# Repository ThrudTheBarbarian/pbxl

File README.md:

# pbxl
Experiment in using an XMOS chip for a low latency serial connection to enable a parallel bus expansion on the Atari XL/XE

# Website
This is very much a work-in-progress, but the website rendered from the source herein [is available here](http://pbxl.oobergeek.net/)

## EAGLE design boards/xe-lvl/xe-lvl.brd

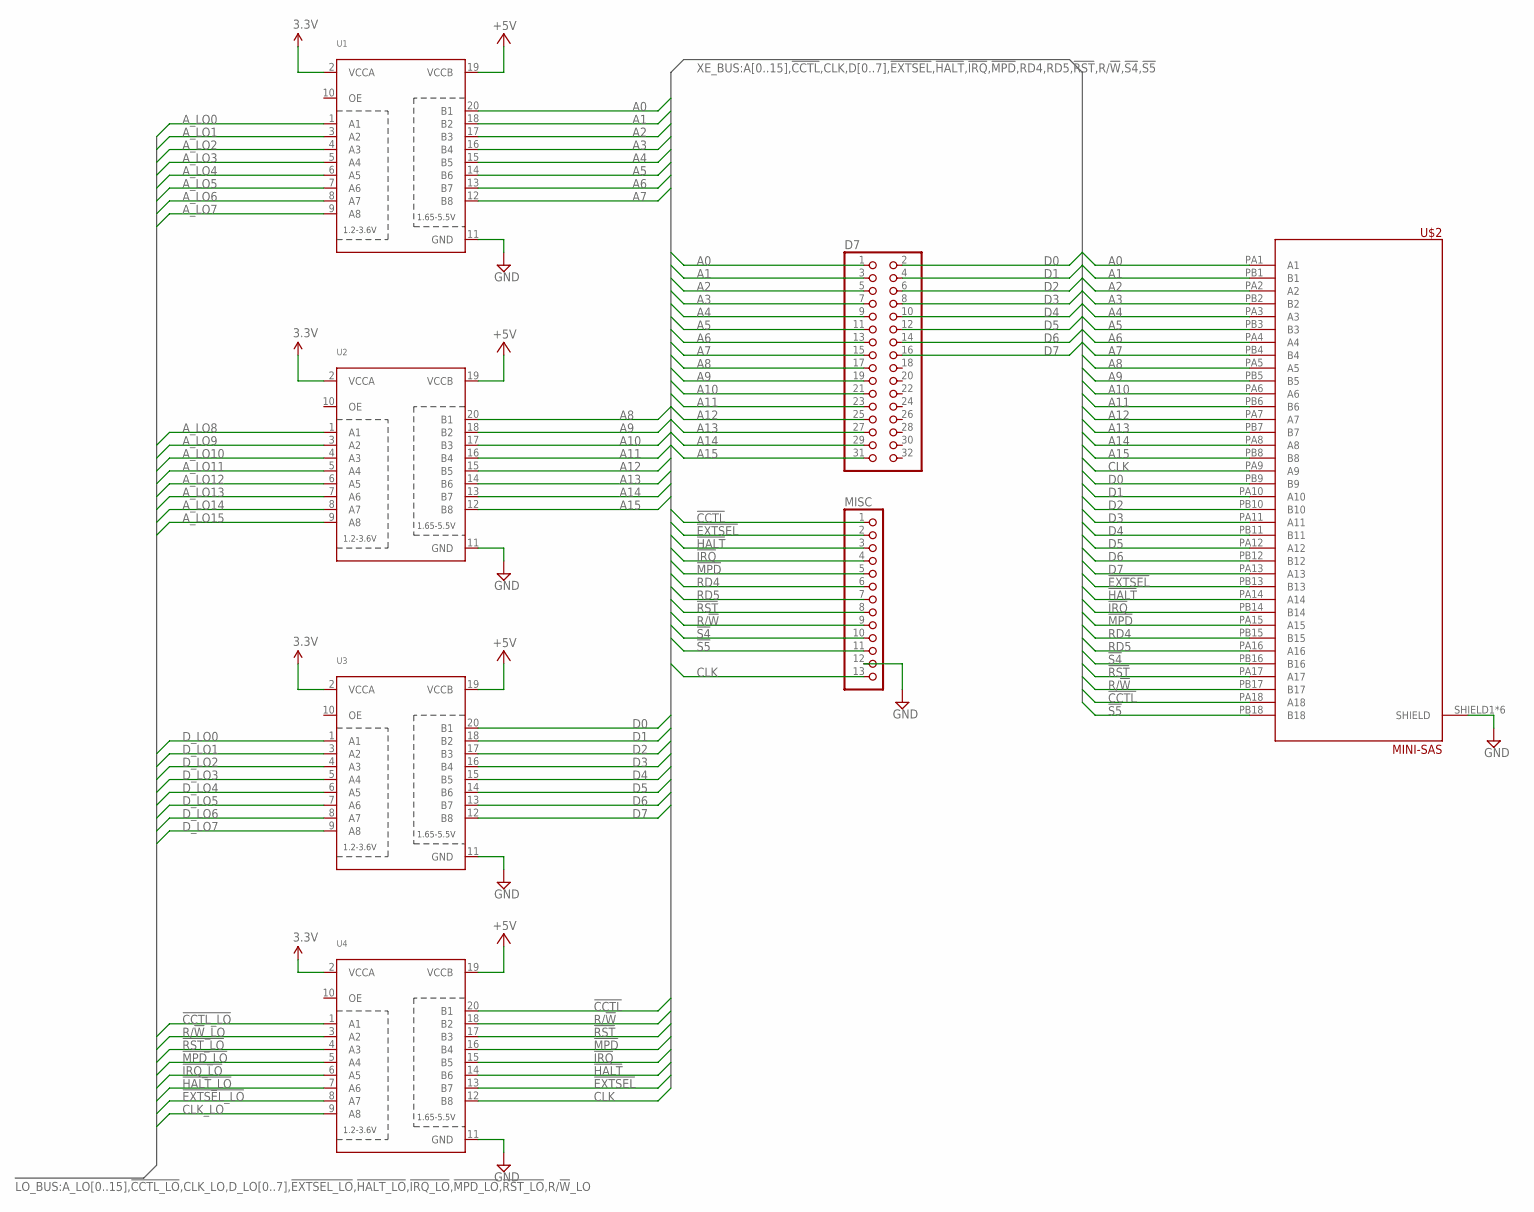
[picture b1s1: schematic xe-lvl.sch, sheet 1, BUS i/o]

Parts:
D7: PINHD-2X16; 2X16
MISC: PINHD-1X13; 1X13
U1, U2, U3, U4: TXB0108PWR; TSSOP20
U$2: MINI-SAS

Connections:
3.3V: U1.2 (VCCA), U2.2 (VCCA), U3.2 (VCCA), U4.2 (VCCA); also elsewhere on the board
!CCTL!: MISC.1, U4.20 (B1), U$2.PA18 (A18)
!CCTL_LO!: U4.1 (A1)
!EXTSEL!: MISC.2, U4.13 (B7), U$2.PB13 (B13)
!EXTSEL_LO!: U4.8 (A7)
!HALT!: MISC.3, U4.14 (B6), U$2.PA14 (A14)
!HALT_LO!: U4.7 (A6)
!IRQ!: MISC.4, U4.15 (B5), U$2.PB14 (B14)
!IRQ_LO!: U4.6 (A5)
!MPD!: MISC.5, U4.16 (B4), U$2.PA15 (A15)
!MPD_LO!: U4.5 (A4)
!RST!: MISC.8, U4.17 (B3), U$2.PA17 (A17); also elsewhere on the board
!RST_LO!: U4.4 (A3)
!S4!: MISC.10, U$2.PB16 (B16)
!S5!: MISC.11, U$2.PB18 (B18)
+5V: U1.19 (VCCB), U2.19 (VCCB), U3.19 (VCCB), U4.19 (VCCB); also elsewhere on the board
A0: D7.1, U1.20 (B1), U$2.PA1 (A1)
A1: D7.3, U1.18 (B2), U$2.PB1 (B1)
A2: D7.5, U1.17 (B3), U$2.PA2 (A2)
A3: D7.7, U1.16 (B4), U$2.PB2 (B2)
A4: D7.9, U1.15 (B5), U$2.PA3 (A3)
A5: D7.11, U1.14 (B6), U$2.PB3 (B3)
A6: D7.13, U1.13 (B7), U$2.PA4 (A4)
A7: D7.15, U1.12 (B8), U$2.PB4 (B4)
A8: D7.17, U2.20 (B1), U$2.PA5 (A5)
A9: D7.19, U2.18 (B2), U$2.PB5 (B5)
A10: D7.21, U2.17 (B3), U$2.PA6 (A6)
A11: D7.23, U2.16 (B4), U$2.PB6 (B6)
A12: D7.25, U2.15 (B5), U$2.PA7 (A7)
A13: D7.27, U2.14 (B6), U$2.PB7 (B7)
A14: D7.29, U2.13 (B7), U$2.PA8 (A8)
A15: D7.31, U2.12 (B8), U$2.PB8 (B8)
A_LO0: U1.1 (A1)
A_LO1: U1.3 (A2)
A_LO2: U1.4 (A3)
A_LO3: U1.5 (A4)
A_LO4: U1.6 (A5)
A_LO5: U1.7 (A6)
A_LO6: U1.8 (A7)
A_LO7: U1.9 (A8)
A_LO8: U2.1 (A1)
A_LO9: U2.3 (A2)
A_LO10: U2.4 (A3)
A_LO11: U2.5 (A4)
A_LO12: U2.6 (A5)
A_LO13: U2.7 (A6)
A_LO14: U2.8 (A7)
A_LO15: U2.9 (A8)
CLK: MISC.13, U4.12 (B8), U$2.PA9 (A9)
CLK_LO: U4.9 (A8)
D0: D7.2, U3.20 (B1), U$2.PB9 (B9)
D1: D7.4, U3.18 (B2), U$2.PA10 (A10)
D2: D7.6, U3.17 (B3), U$2.PB10 (B10)
D3: D7.8, U3.16 (B4), U$2.PA11 (A11)
D4: D7.10, U3.15 (B5), U$2.PB11 (B11)
D5: D7.12, U3.14 (B6), U$2.PA12 (A12)
D6: D7.14, U3.13 (B7), U$2.PB12 (B12)
D7: D7.16, U3.12 (B8), U$2.PA13 (A13)
D_LO0: U3.1 (A1)
D_LO1: U3.3 (A2)
D_LO2: U3.4 (A3)
D_LO3: U3.5 (A4)
D_LO4: U3.6 (A5)
D_LO5: U3.7 (A6)
D_LO6: U3.8 (A7)
D_LO7: U3.9 (A8)
GND: MISC.12, U1.11 (GND), U2.11 (GND), U3.11 (GND), U4.11 (GND), U$2.SHIELD1 (SHIELD), U$2.SHIELD2 (SHIELD), U$2.SHIELD3 (SHIELD), U$2.SHIELD4 (SHIELD), U$2.SHIELD5 (SHIELD), U$2.SHIELD6 (SHIELD); also elsewhere on the board
R/!W!: MISC.9, U4.18 (B2), U$2.PB17 (B17)
R/!W!_LO: U4.3 (A2)
RD4: MISC.6, U$2.PB15 (B15)
RD5: MISC.7, U$2.PA16 (A16)

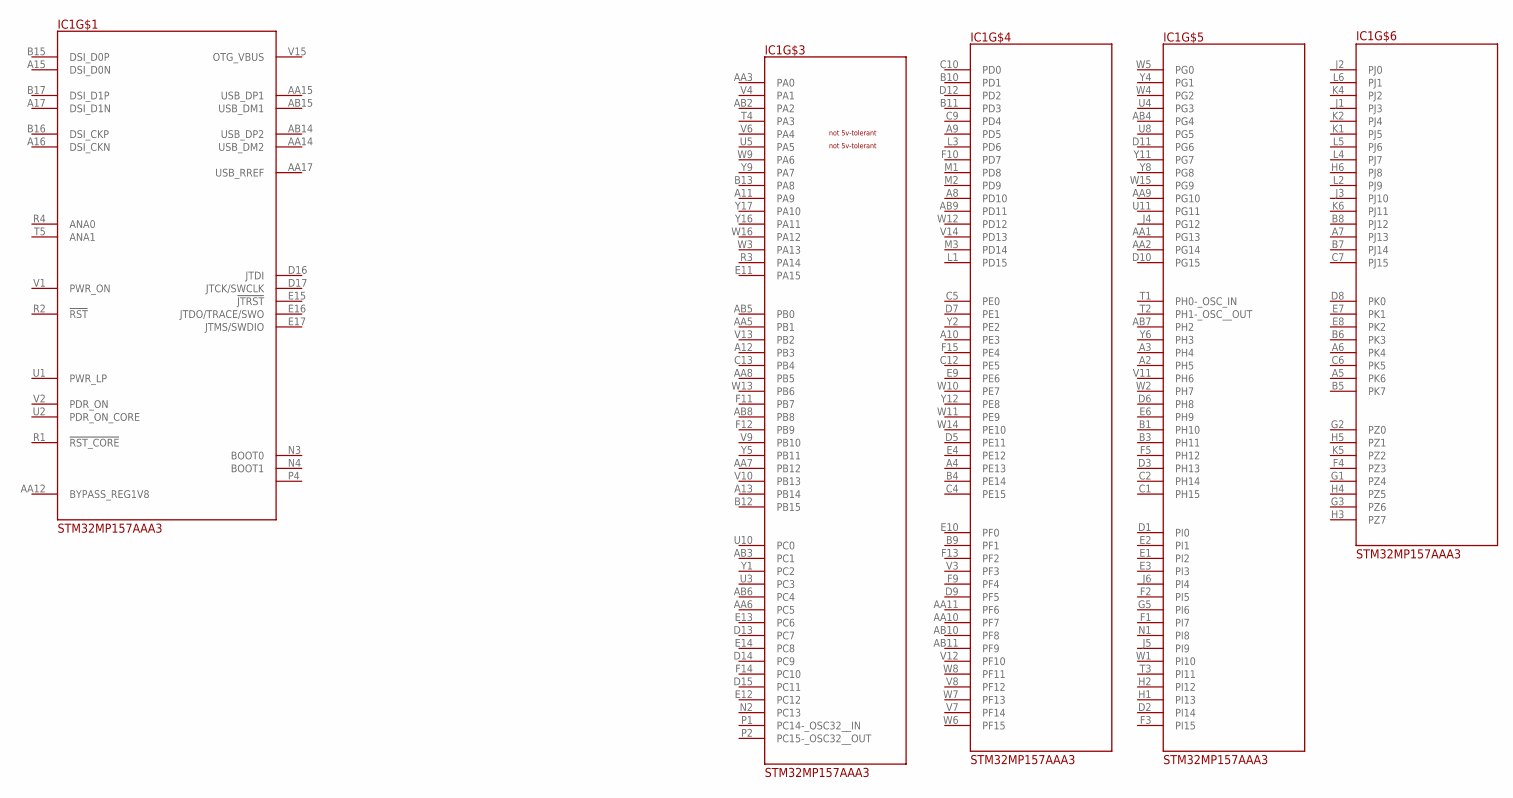
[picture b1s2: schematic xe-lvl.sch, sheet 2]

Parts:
IC1: STM32MP157AAA3; BGA448C80P22X22_1800X1800X127

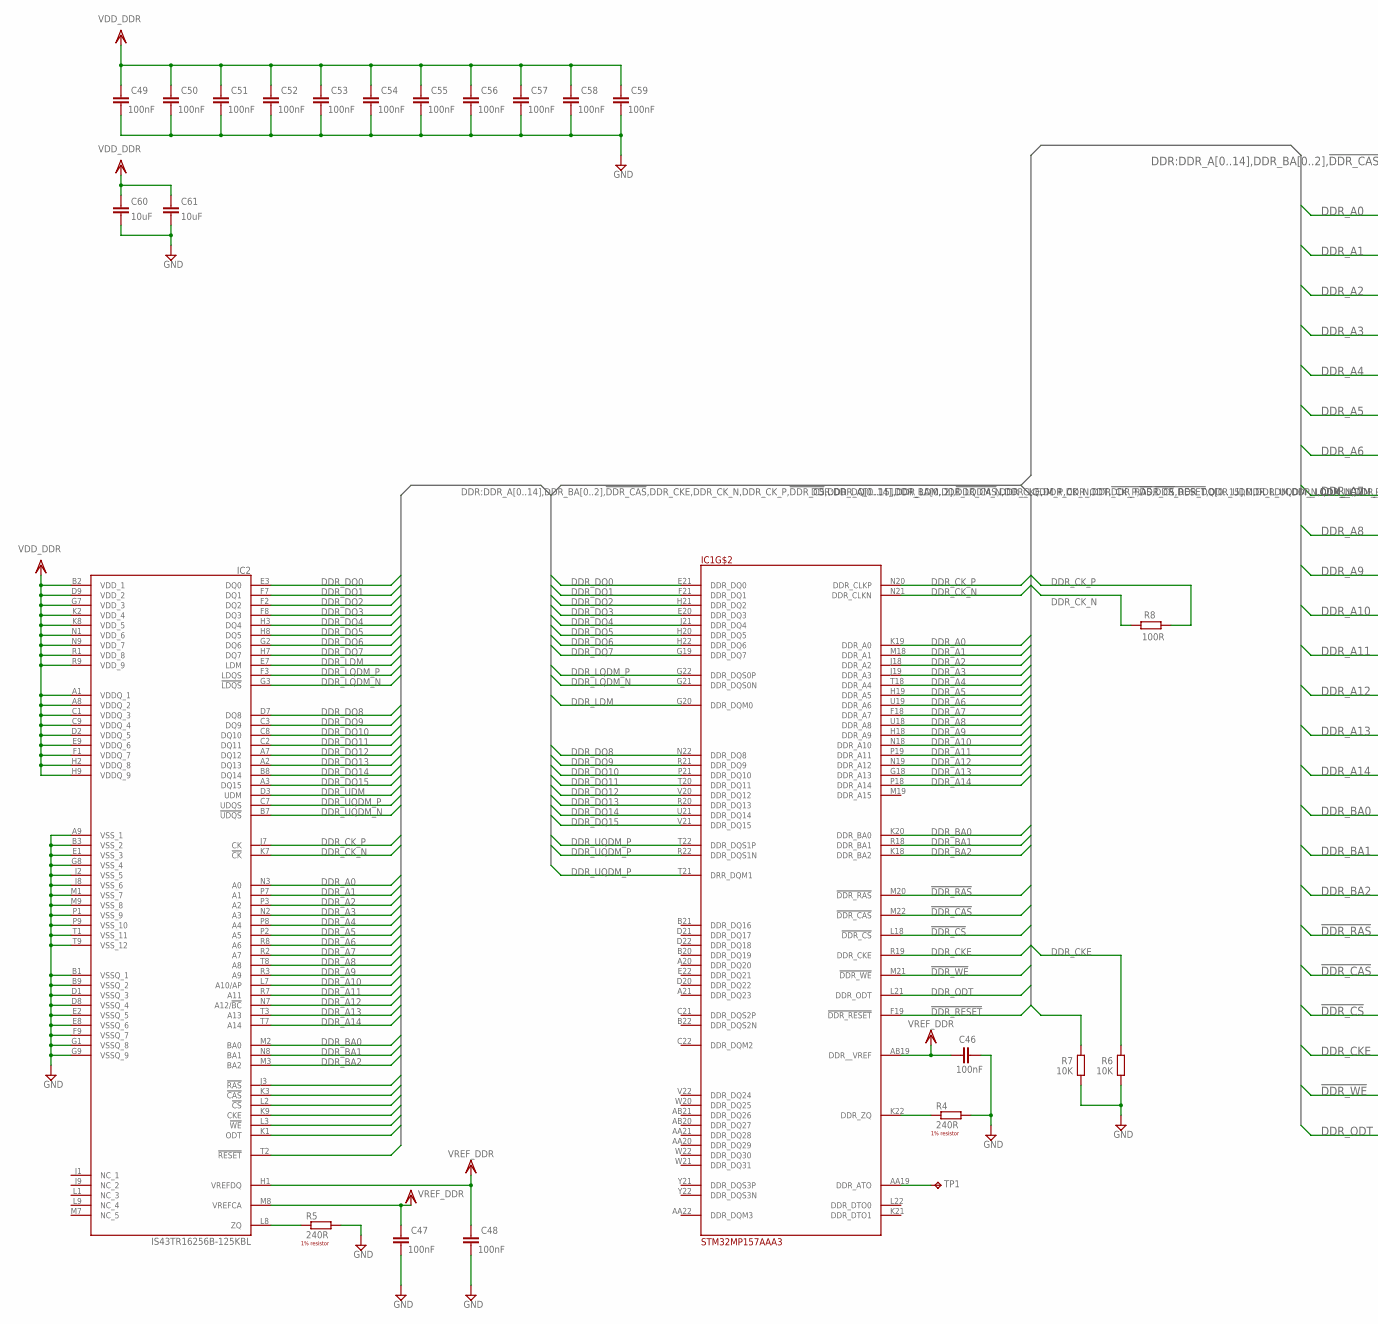
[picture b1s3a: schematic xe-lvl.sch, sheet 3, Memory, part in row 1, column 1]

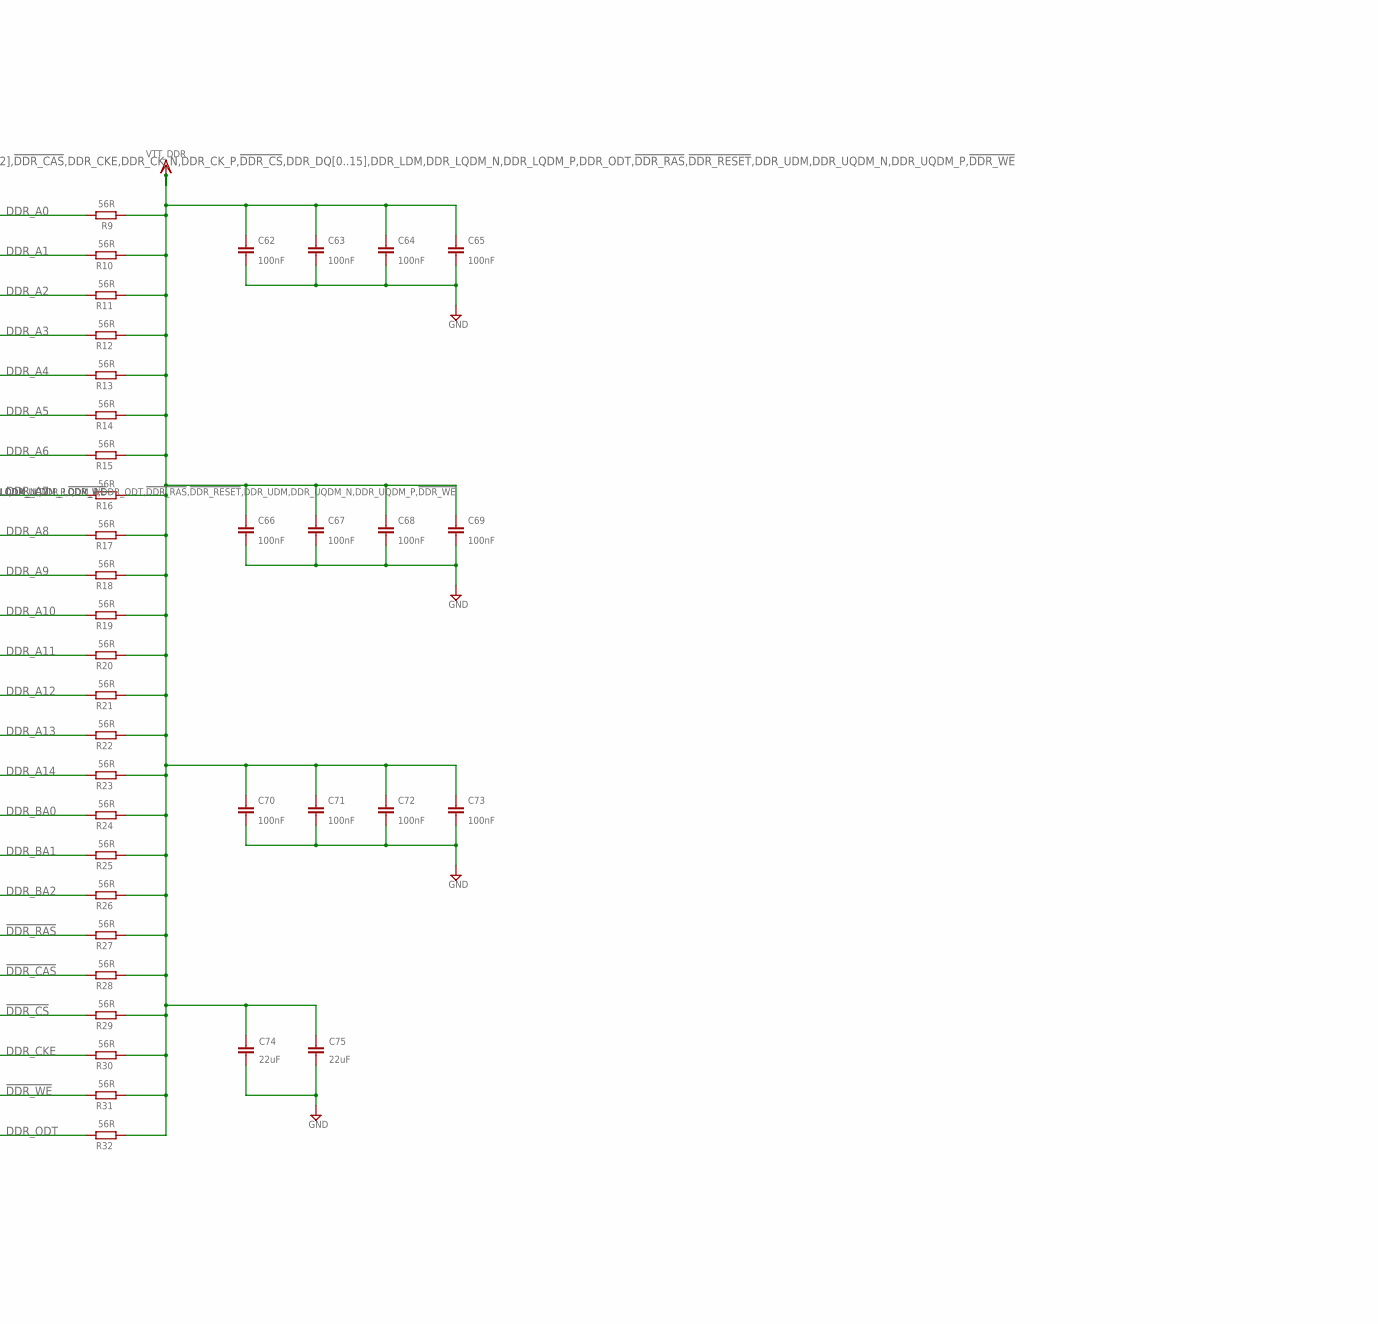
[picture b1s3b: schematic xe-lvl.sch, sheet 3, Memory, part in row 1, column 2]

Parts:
C46, C47, C48, C49, C50, C51, C52, C53, C54, C55, C56, C57, C58, C59, C62, C63, C64, C65, C66, C67, C68, C69, C70, C71, C72, C73: 100nF; C0201
C60, C61: 10uF; C0402
C74, C75: 22uF; C0402
IC1: STM32MP157AAA3; BGA448C80P22X22_1800X1800X127
IC2: IS43TR16256B-125KBL; BGA96C80P9X16_800X1400X120
R4, R5: 240R; R0201
R6, R7: 10K; R0201
R8: 100R; R0201
R9, R10, R11, R12, R13, R14, R15, R16, R17, R18, R19, R20, R21, R22, R23, R24, R25, R26, R27, R28, R29, R30, R31, R32: 56R; R0201
TP1: TPB1,27; B1,27

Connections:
!DDR_CAS!: IC1.M22 (!DDR_CAS!), IC2.K3 (!CAS!), R28.1
!DDR_CS!: IC1.L18 (!DDR_CS!), IC2.L2 (!CS!), R29.1
!DDR_RAS!: IC1.M20 (!DDR_RAS!), IC2.J3 (!RAS!), R27.1
!DDR_RESET!: IC1.F19 (!DDR_RESET!), IC2.T2 (!RESET!), R7.2
!DDR_WE!: IC1.M21 (!DDR_WE!), IC2.L3 (!WE!), R31.1
DDR_A0: IC1.K19 (DDR_A0), IC2.N3 (A0), R9.1
DDR_A1: IC1.M18 (DDR_A1), IC2.P7 (A1), R10.1
DDR_A2: IC1.J18 (DDR_A2), IC2.P3 (A2), R11.1
DDR_A3: IC1.J19 (DDR_A3), IC2.N2 (A3), R12.1
DDR_A4: IC1.T18 (DDR_A4), IC2.P8 (A4), R13.1
DDR_A5: IC1.H19 (DDR_A5), IC2.P2 (A5), R14.1
DDR_A6: IC1.U19 (DDR_A6), IC2.R8 (A6), R15.1
DDR_A7: IC1.F18 (DDR_A7), IC2.R2 (A7), R16.1
DDR_A8: IC1.U18 (DDR_A8), IC2.T8 (A8), R17.1
DDR_A9: IC1.H18 (DDR_A9), IC2.R3 (A9), R18.1
DDR_A10: IC1.N18 (DDR_A10), IC2.L7 (A10/AP), R19.1
DDR_A11: IC1.P19 (DDR_A11), IC2.R7 (A11), R20.1
DDR_A12: IC1.N19 (DDR_A12), IC2.N7 (A12/!BC!), R21.1
DDR_A13: IC1.G18 (DDR_A13), IC2.T3 (A13), R22.1
DDR_A14: IC1.P18 (DDR_A14), IC2.T7 (A14), R23.1
DDR_BA0: IC1.K20 (DDR_BA0), IC2.M2 (BA0), R24.1
DDR_BA1: IC1.R18 (DDR_BA1), IC2.N8 (BA1), R25.1
DDR_BA2: IC1.K18 (DDR_BA2), IC2.M3 (BA2), R26.1
DDR_CKE: IC1.R19 (DDR_CKE), IC2.K9 (CKE), R6.2, R30.1
DDR_CK_N: IC1.N21 (DDR_CLKN), IC2.K7 (!CK!), R8.2
DDR_CK_P: IC1.N20 (DDR_CLKP), IC2.J7 (CK), R8.1
DDR_DQ0: IC1.E21 (DDR_DQ0), IC2.E3 (DQ0)
DDR_DQ1: IC1.F21 (DDR_DQ1), IC2.F7 (DQ1)
DDR_DQ2: IC1.H21 (DDR_DQ2), IC2.F2 (DQ2)
DDR_DQ3: IC1.E20 (DDR_DQ3), IC2.F8 (DQ3)
DDR_DQ4: IC1.J21 (DDR_DQ4), IC2.H3 (DQ4)
DDR_DQ5: IC1.H20 (DDR_DQ5), IC2.H8 (DQ5)
DDR_DQ6: IC1.H22 (DDR_DQ6), IC2.G2 (DQ6)
DDR_DQ7: IC1.G19 (DDR_DQ7), IC2.H7 (DQ7)
DDR_DQ8: IC1.N22 (DDR_DQ8), IC2.D7 (DQ8)
DDR_DQ9: IC1.R21 (DDR_DQ9), IC2.C3 (DQ9)
DDR_DQ10: IC1.P21 (DDR_DQ10), IC2.C8 (DQ10)
DDR_DQ11: IC1.T20 (DDR_DQ11), IC2.C2 (DQ11)
DDR_DQ12: IC1.V20 (DDR_DQ12), IC2.A7 (DQ12)
DDR_DQ13: IC1.R20 (DDR_DQ13), IC2.A2 (DQ13)
DDR_DQ14: IC1.U21 (DDR_DQ14), IC2.B8 (DQ14)
DDR_DQ15: IC1.V21 (DDR_DQ15), IC2.A3 (DQ15)
DDR_LDM: IC1.G20 (DDR_DQM0), IC2.E7 (LDM)
DDR_LQDM_N: IC1.G21 (DDR_DQS0N), IC2.G3 (!LDQS!)
DDR_LQDM_P: IC1.G22 (DDR_DQS0P), IC2.F3 (LDQS)
DDR_ODT: IC1.L21 (DDR_ODT), IC2.K1 (ODT), R32.1
DDR_UDM: IC1.T21 (DRR_DQM1), IC2.D3 (UDM)
DDR_UQDM_N: IC1.R22 (DDR_DQS1N), IC2.B7 (!UDQS!)
DDR_UQDM_P: IC1.T22 (DDR_DQS1P), IC2.C7 (UDQS)
GND: C46.2, C47.1, C48.1, C49.1, C50.1, C51.1, C52.1, C53.1, C54.1, C55.1, C56.1, C57.1, C58.1, C59.1, C60.2, C61.2, C62.1, C63.1, C64.1, C65.1, C66.1, C67.1, C68.1, C69.1, C70.1, C71.1, C72.1, C73.1, C74.1, C75.1, IC2.A9 (VSS_1), IC2.B1 (VSSQ_1), IC2.B3 (VSS_2), IC2.B9 (VSSQ_2), IC2.D1 (VSSQ_3), IC2.D8 (VSSQ_4), IC2.E1 (VSS_3), IC2.E2 (VSSQ_5), IC2.E8 (VSSQ_6), IC2.F9 (VSSQ_7), IC2.G1 (VSSQ_8), IC2.G8 (VSS_4), IC2.G9 (VSSQ_9), IC2.J2 (VSS_5), IC2.J8 (VSS_6), IC2.M1 (VSS_7), IC2.M9 (VSS_8), IC2.P1 (VSS_9), IC2.P9 (VSS_10), IC2.T1 (VSS_11), IC2.T9 (VSS_12), R4.2, R5.2, R6.1, R7.1; also elsewhere on the board
unnamed: IC1.K22 (DDR_ZQ), R4.1
unnamed: IC1.AA19 (DDR_ATO), TP1.TP
unnamed: IC2.L8 (ZQ), R5.1
VDD_DDR: C49.2, C50.2, C51.2, C52.2, C53.2, C54.2, C55.2, C56.2, C57.2, C58.2, C59.2, C60.1, C61.1, IC2.A1 (VDDQ_1), IC2.A8 (VDDQ_2), IC2.B2 (VDD_1), IC2.C1 (VDDQ_3), IC2.C9 (VDDQ_4), IC2.D2 (VDDQ_5), IC2.D9 (VDD_2), IC2.E9 (VDDQ_6), IC2.F1 (VDDQ_7), IC2.G7 (VDD_3), IC2.H2 (VDDQ_8), IC2.H9 (VDDQ_9), IC2.K2 (VDD_4), IC2.K8 (VDD_5), IC2.N1 (VDD_6), IC2.N9 (VDD_7), IC2.R1 (VDD_8), IC2.R9 (VDD_9); also elsewhere on the board
VREF_DDR: C46.1, C47.2, C48.2, IC1.AB19 (DDR__VREF), IC2.H1 (VREFDQ), IC2.M8 (VREFCA); also elsewhere on the board
VTT_DDR: C62.2, C63.2, C64.2, C65.2, C66.2, C67.2, C68.2, C69.2, C70.2, C71.2, C72.2, C73.2, C74.2, C75.2, R9.2, R10.2, R11.2, R12.2, R13.2, R14.2, R15.2, R16.2, R17.2, R18.2, R19.2, R20.2, R21.2, R22.2, R23.2, R24.2, R25.2, R26.2, R27.2, R28.2, R29.2, R30.2, R31.2, R32.2; also elsewhere on the board

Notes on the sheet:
1% resistor

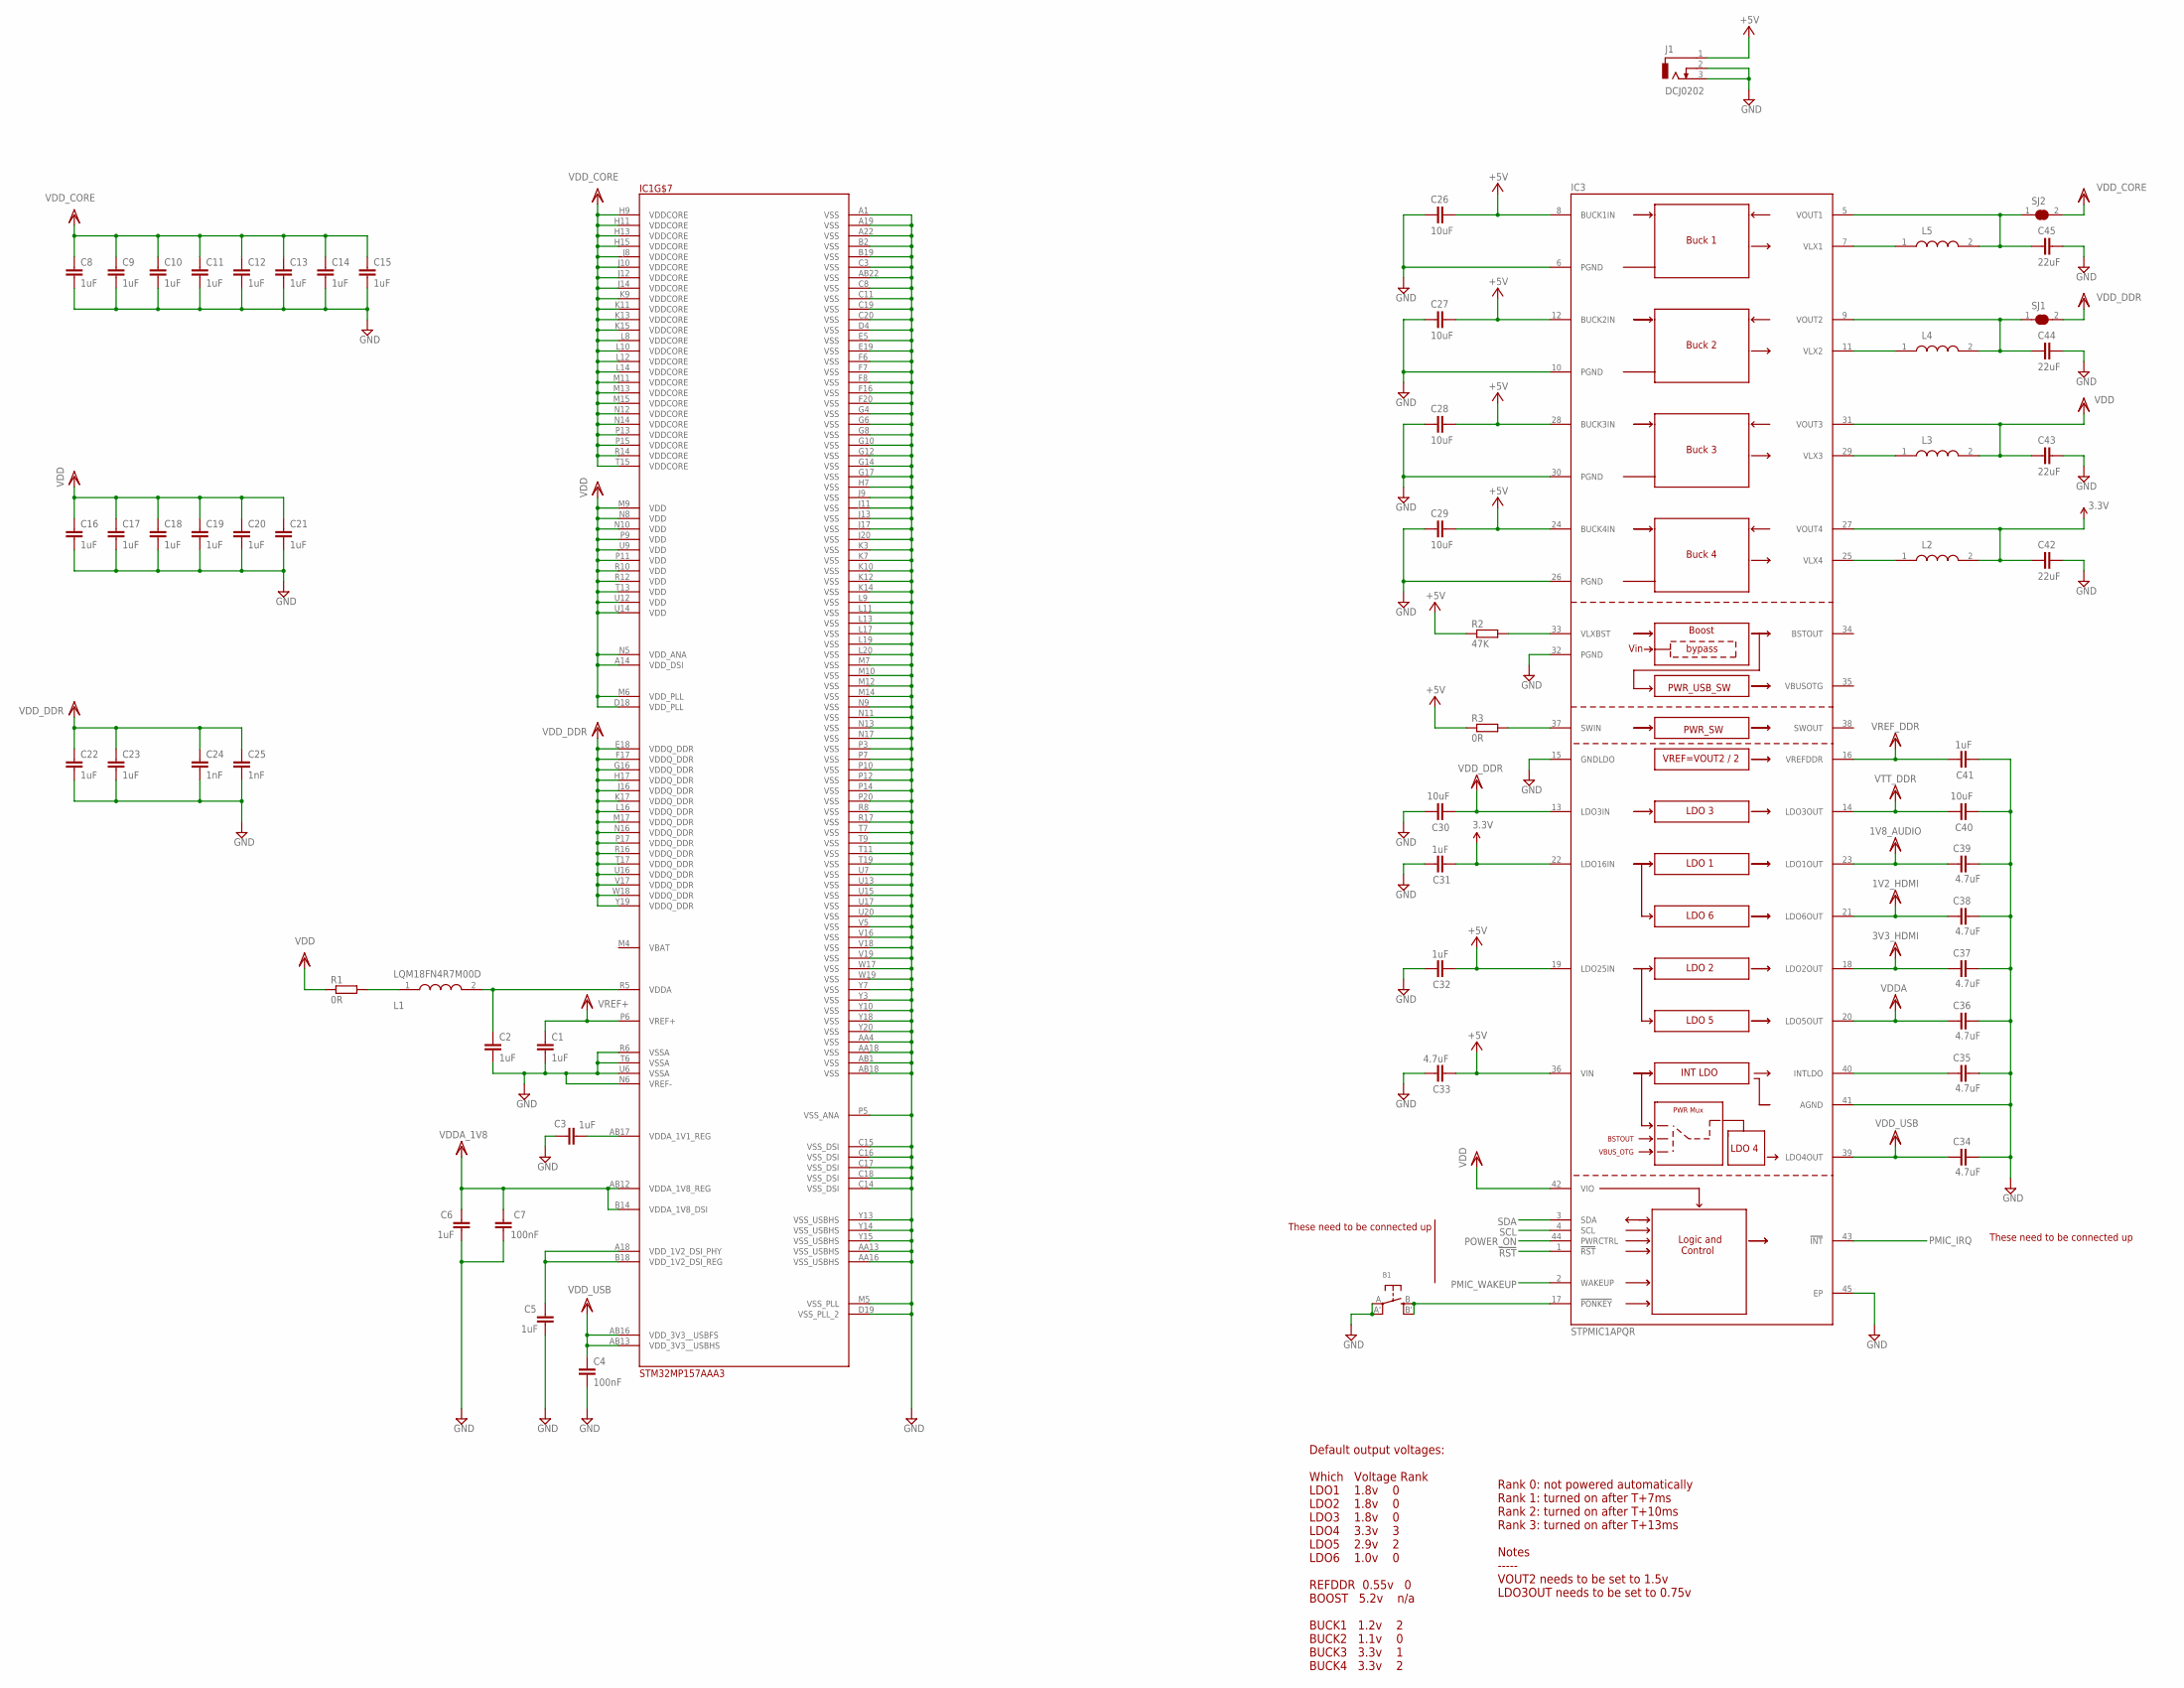
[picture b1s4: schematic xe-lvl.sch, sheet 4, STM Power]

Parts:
B1: SWITCH_TACT_SMT; EVQ-Q2
C1, C2, C3, C5, C6, C8, C9, C10, C11, C12, C13, C14, C15, C16, C17, C18, C19, C20, C21, C22, C23, C31, C32, C41: 1uF; C0201
C4, C7: 100nF; C0201
C24, C25: 1nF; C0201
C26, C27, C28, C29, C30, C40: 10uF; C0402
C33, C34, C35, C36, C37, C38, C39: 4.7uF; C0201
C42, C43, C44, C45: 22uF; C0402
IC1: STM32MP157AAA3; BGA448C80P22X22_1800X1800X127
IC3: STPMIC1APQR; QFN40P500X600X80-45N
J1: DCJ0202
L1: LQM18FN4R7M00D; INDC1608X90N
L2, L3, L4, L5: DFE252012P-1ROM=P2; INDC2520X120N
R1, R3: 0R; R0201
R2: 47K; R0201
SJ1, SJ2: SOLDERJUMPER_CLOSEDPERM

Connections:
1V2_HDMI: C38.1, IC3.21 (LDO6OUT)
1V8_AUDIO: C39.1, IC3.23 (LDO1OUT)
3.3V: C31.1, C42.1, IC3.22 (LDO16IN), IC3.27 (VOUT4), L2.2; also elsewhere on the board
3V3_HDMI: C37.1, IC3.18 (LDO2OUT)
!RST!: IC3.1 (!RST!); also elsewhere on the board
+5V: C26.2, C27.2, C28.2, C29.2, C32.1, C33.1, IC3.8 (BUCK1IN), IC3.12 (BUCK2IN), IC3.19 (LDO25IN), IC3.24 (BUCK4IN), IC3.28 (BUCK3IN), IC3.36 (VIN), J1.1, R2.1, R3.1; also elsewhere on the board
GND: B1.A, B1.A' (P1), C1.2, C2.2, C3.1, C4.2, C5.1, C6.1, C7.1, C8.2, C9.2, C10.2, C11.2, C12.2, C13.2, C14.2, C15.2, C16.2, C17.2, C18.2, C19.2, C20.2, C21.2, C22.2, C23.2, C24.2, C25.2, C26.1, C27.1, C28.1, C29.1, C30.2, C31.2, C32.2, C33.2, C34.2, C35.2, C36.2, C37.2, C38.2, C39.2, C40.1, C41.1, C42.2, C43.2, C44.2, C45.2, IC1.A1 (VSS), IC1.A19 (VSS), IC1.A22 (VSS), IC1.AA4 (VSS), IC1.AA13 (VSS_USBHS), IC1.AA16 (VSS_USBHS), IC1.AA18 (VSS), IC1.AB1 (VSS), IC1.AB18 (VSS), IC1.AB22 (VSS), IC1.B2 (VSS), IC1.B19 (VSS), IC1.C3 (VSS), IC1.C8 (VSS), IC1.C11 (VSS), IC1.C14 (VSS_DSI), IC1.C15 (VSS_DSI), IC1.C16 (VSS_DSI), IC1.C17 (VSS_DSI), IC1.C18 (VSS_DSI), IC1.C19 (VSS), IC1.C20 (VSS), IC1.D4 (VSS), IC1.D19 (VSS_PLL_2), IC1.E5 (VSS), IC1.E19 (VSS), IC1.F6 (VSS), IC1.F7 (VSS), IC1.F8 (VSS), IC1.F16 (VSS), IC1.F20 (VSS), IC1.G4 (VSS), IC1.G6 (VSS), IC1.G8 (VSS), IC1.G10 (VSS), IC1.G12 (VSS), IC1.G14 (VSS), IC1.G17 (VSS), IC1.H7 (VSS), IC1.J9 (VSS), IC1.J11 (VSS), IC1.J13 (VSS), IC1.J17 (VSS), IC1.J20 (VSS), IC1.K3 (VSS), IC1.K7 (VSS), IC1.K10 (VSS), IC1.K12 (VSS), IC1.K14 (VSS), IC1.L9 (VSS), IC1.L11 (VSS), IC1.L13 (VSS), IC1.L17 (VSS), IC1.L19 (VSS), IC1.L20 (VSS), IC1.M5 (VSS_PLL), IC1.M7 (VSS), IC1.M10 (VSS), IC1.M12 (VSS), IC1.M14 (VSS), IC1.N6 (VREF-), IC1.N9 (VSS), IC1.N11 (VSS), IC1.N13 (VSS), IC1.N17 (VSS), IC1.P3 (VSS), IC1.P5 (VSS_ANA), IC1.P7 (VSS), IC1.P10 (VSS), IC1.P12 (VSS), IC1.P14 (VSS), IC1.P20 (VSS), IC1.R6 (VSSA), IC1.R8 (VSS), IC1.R17 (VSS), IC1.T6 (VSSA), IC1.T7 (VSS), IC1.T9 (VSS), IC1.T11 (VSS), IC1.T19 (VSS), IC1.U6 (VSSA), IC1.U7 (VSS), IC1.U13 (VSS), IC1.U15 (VSS), IC1.U17 (VSS), IC1.U20 (VSS), IC1.V5 (VSS), IC1.V16 (VSS), IC1.V18 (VSS), IC1.V19 (VSS), IC1.W17 (VSS), IC1.W19 (VSS), IC1.Y3 (VSS), IC1.Y7 (VSS), IC1.Y10 (VSS), IC1.Y13 (VSS_USBHS), IC1.Y14 (VSS_USBHS), IC1.Y15 (VSS_USBHS), IC1.Y18 (VSS), IC1.Y20 (VSS), IC3.6 (PGND), IC3.10 (PGND), IC3.15 (GNDLDO), IC3.26 (PGND), IC3.30 (PGND), IC3.32 (PGND), IC3.41 (AGND), IC3.45 (EP), J1.2, J1.3; also elsewhere on the board
unnamed: C2.1, IC1.R5 (VDDA), L1.2
unnamed: L1.1, R1.2
unnamed: C3.2, IC1.AB17 (VDDA_1V1_REG)
unnamed: C5.2, IC1.A18 (VDD_1V2_DSI_PHY), IC1.B18 (VDD_1V2_DSI_REG)
unnamed: IC3.33 (VLXBST), R2.2
unnamed: B1.B (S), B1.B' (S1), IC3.17 (!PONKEY!)
unnamed: IC3.37 (SWIN), R3.2
unnamed: C35.1, IC3.40 (INTLDO)
unnamed: IC3.25 (VLX4), L2.1
unnamed: IC3.29 (VLX3), L3.1
unnamed: IC3.11 (VLX2), L4.1
unnamed: C44.1, IC3.9 (VOUT2), L4.2, SJ1.1
unnamed: IC3.7 (VLX1), L5.1
unnamed: C45.1, IC3.5 (VOUT1), L5.2, SJ2.1
PMIC_IRQ: IC3.43 (!INT!)
PMIC_WAKEUP: IC3.2 (WAKEUP)
POWER_ON: IC3.44 (PWRCTRL)
SCL: IC3.4 (SCL)
SDA: IC3.3 (SDA)
VDD: C16.1, C17.1, C18.1, C19.1, C20.1, C21.1, C43.1, IC1.A14 (VDD_DSI), IC1.D18 (VDD_PLL), IC1.M6 (VDD_PLL), IC1.M9 (VDD), IC1.N5 (VDD_ANA), IC1.N8 (VDD), IC1.N10 (VDD), IC1.P9 (VDD), IC1.P11 (VDD), IC1.R10 (VDD), IC1.R12 (VDD), IC1.T13 (VDD), IC1.U9 (VDD), IC1.U12 (VDD), IC1.U14 (VDD), IC3.31 (VOUT3), IC3.42 (VIO), L3.2, R1.1
VDDA: C36.1, IC3.20 (LDO5OUT)
VDDA_1V8: C6.2, C7.2, IC1.AB12 (VDDA_1V8_REG), IC1.B14 (VDDA_1V8_DSI)
VDD_CORE: C8.1, C9.1, C10.1, C11.1, C12.1, C13.1, C14.1, C15.1, IC1.H9 (VDDCORE), IC1.H11 (VDDCORE), IC1.H13 (VDDCORE), IC1.H15 (VDDCORE), IC1.J8 (VDDCORE), IC1.J10 (VDDCORE), IC1.J12 (VDDCORE), IC1.J14 (VDDCORE), IC1.K9 (VDDCORE), IC1.K11 (VDDCORE), IC1.K13 (VDDCORE), IC1.K15 (VDDCORE), IC1.L8 (VDDCORE), IC1.L10 (VDDCORE), IC1.L12 (VDDCORE), IC1.L14 (VDDCORE), IC1.M11 (VDDCORE), IC1.M13 (VDDCORE), IC1.M15 (VDDCORE), IC1.N12 (VDDCORE), IC1.N14 (VDDCORE), IC1.P13 (VDDCORE), IC1.P15 (VDDCORE), IC1.R14 (VDDCORE), IC1.T15 (VDDCORE), SJ2.2
VDD_DDR: C22.1, C23.1, C24.1, C25.1, C30.1, IC1.E18 (VDDQ_DDR), IC1.F17 (VDDQ_DDR), IC1.G16 (VDDQ_DDR), IC1.H17 (VDDQ_DDR), IC1.J16 (VDDQ_DDR), IC1.K17 (VDDQ_DDR), IC1.L16 (VDDQ_DDR), IC1.M17 (VDDQ_DDR), IC1.N16 (VDDQ_DDR), IC1.P17 (VDDQ_DDR), IC1.R16 (VDDQ_DDR), IC1.T17 (VDDQ_DDR), IC1.U16 (VDDQ_DDR), IC1.V17 (VDDQ_DDR), IC1.W18 (VDDQ_DDR), IC1.Y19 (VDDQ_DDR), IC3.13 (LDO3IN), SJ1.2; also elsewhere on the board
VDD_USB: C4.1, C34.1, IC1.AB13 (VDD_3V3__USBHS), IC1.AB16 (VDD_3V3__USBFS), IC3.39 (LDO4OUT)
VREF+: C1.1, IC1.P6 (VREF+)
VREF_DDR: C41.2, IC3.16 (VREFDDR); also elsewhere on the board
VTT_DDR: C40.2, IC3.14 (LDO3OUT); also elsewhere on the board

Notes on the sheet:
These need to be connected up
Default output voltages: Which Voltage Rank LDO1 1.8v 0 LDO2 1.8v 0 LDO3 1.8v 0 LDO4 3.3v 3 LDO5 2.9v 2 LDO6 1.0v 0 REFDDR 0.55v 0 BOOST 5.2v n/a BUCK1 1.2v 2 BUCK2 1.1v 0 BUCK3 3.3v 1 BUCK4 3.3v 2
Rank 0: not powered automatically Rank 1: turned on after T+7ms Rank 2: turned on after T+10ms Rank 3: turned on after T+13ms Notes ----- VOUT2 needs to be set to 1.5v LDO3OUT needs to be set to 0.75v

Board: 4 copper layers, 127 parts (48 on the bottom side), 117 nets, no tracks yet.

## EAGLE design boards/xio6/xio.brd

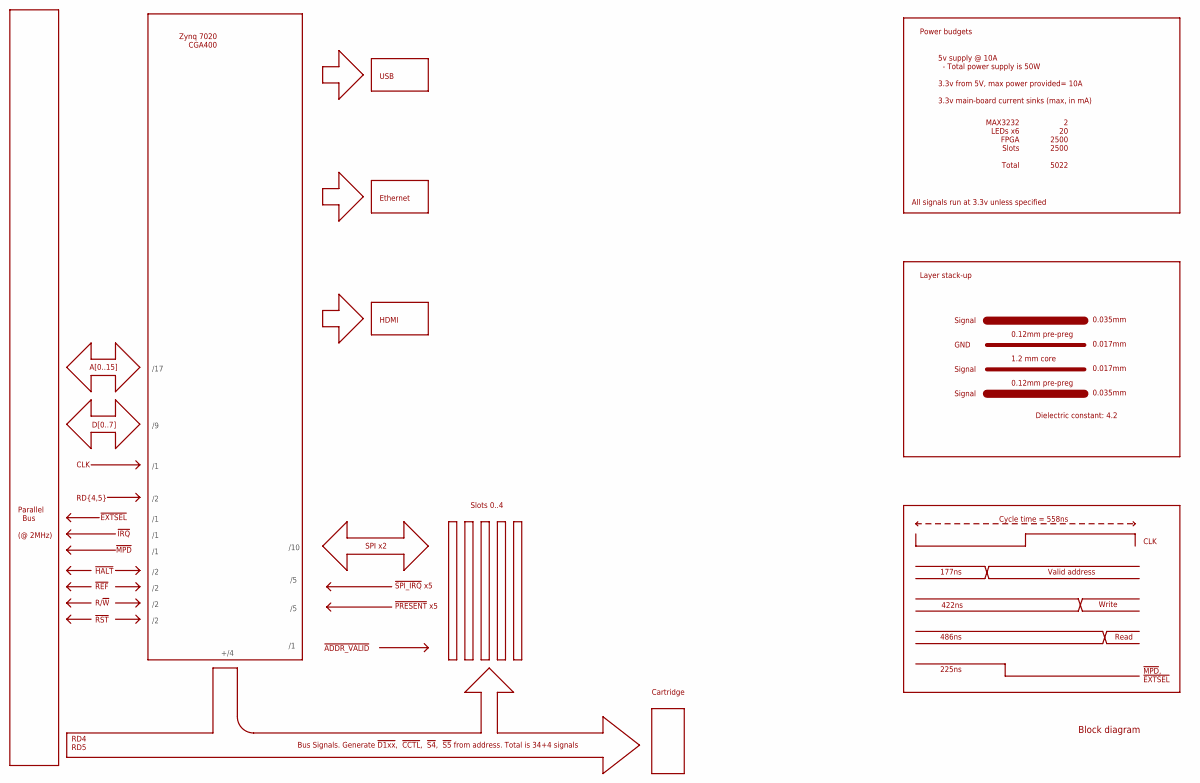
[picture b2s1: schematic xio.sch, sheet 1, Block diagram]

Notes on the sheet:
Slots 0..4
Bus Signals. Generate !D1xx!, !CCTL!, !S4!, !S5! from address. Total is 34+4 signals
5v supply @ 10A - Total power supply is 50W 3.3v from 5V, max power provided= 10A 3.3v main-board current sinks (max, in mA)
MAX3232 LEDs x6 FPGA Slots Total
2 20 2500 2500 5022
1.2 mm core
0.12mm pre-preg
0.035mm
0.017mm
Layer stack-up
GND
Dielectric constant: 4.2
Cycle time = 558ns
Valid address
Write
Read
177ns
422ns
486ns
225ns
!MPD!, !EXTSEL!
CLK
Power budgets
Zynq 7020 CGA400
HDMI
Signal
Block diagram
Parallel Bus (@ 2MHz)
A[0..15]
D[0..7]
RD{4,5}
!MPD!
!IRQ!
!EXTSEL!
!HALT!
!REF!
R/!W!
/17
!ADDR_VALID!
+/4

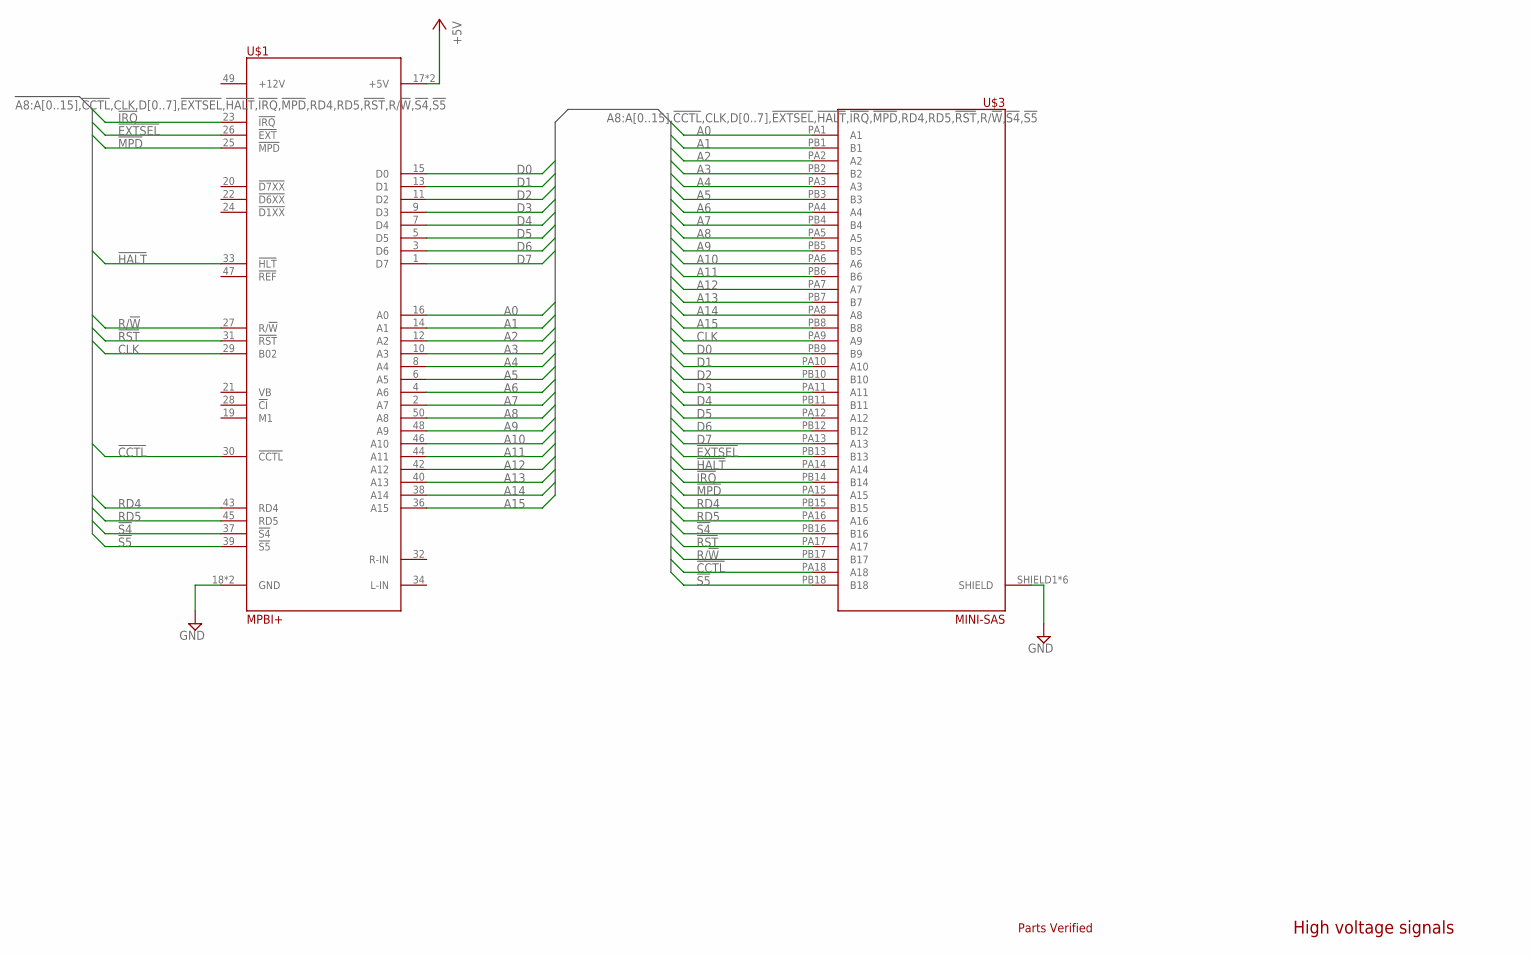
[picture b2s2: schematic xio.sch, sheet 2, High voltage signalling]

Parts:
U$1: MPBI+; 2X25
U$3: MINI-SAS

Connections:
!CCTL!: U$1.30 (!CCTL!), U$3.PA18 (A18)
!EXTSEL!: U$1.26 (!EXT!), U$3.PB13 (B13)
!HALT!: U$1.33 (!HLT!), U$3.PA14 (A14)
!IRQ!: U$1.23 (!IRQ!), U$3.PB14 (B14)
!MPD!: U$1.25 (!MPD!), U$3.PA15 (A15)
!RST!: U$1.31 (!RST!), U$3.PA17 (A17)
!S4!: U$1.37 (!S4!), U$3.PB16 (B16)
!S5!: U$1.39 (!S5!), U$3.PB18 (B18)
+5V: U$1.17 (+5V), U$1.41 (+5V); also elsewhere on the board
A0: U$1.16 (A0), U$3.PA1 (A1); also elsewhere on the board
A1: U$1.14 (A1), U$3.PB1 (B1); also elsewhere on the board
A2: U$1.12 (A2), U$3.PA2 (A2); also elsewhere on the board
A3: U$1.10 (A3), U$3.PB2 (B2); also elsewhere on the board
A4: U$1.8 (A4), U$3.PA3 (A3); also elsewhere on the board
A5: U$1.6 (A5), U$3.PB3 (B3); also elsewhere on the board
A6: U$1.4 (A6), U$3.PA4 (A4); also elsewhere on the board
A7: U$1.2 (A7), U$3.PB4 (B4); also elsewhere on the board
A8: U$1.50 (A8), U$3.PA5 (A5); also elsewhere on the board
A9: U$1.48 (A9), U$3.PB5 (B5); also elsewhere on the board
A10: U$1.46 (A10), U$3.PA6 (A6); also elsewhere on the board
A11: U$1.44 (A11), U$3.PB6 (B6); also elsewhere on the board
A12: U$1.42 (A12), U$3.PA7 (A7); also elsewhere on the board
A13: U$1.40 (A13), U$3.PB7 (B7); also elsewhere on the board
A14: U$1.38 (A14), U$3.PA8 (A8); also elsewhere on the board
A15: U$1.36 (A15), U$3.PB8 (B8); also elsewhere on the board
CLK: U$1.29 (B02), U$3.PA9 (A9)
D0: U$1.15 (D0), U$3.PB9 (B9); also elsewhere on the board
D1: U$1.13 (D1), U$3.PA10 (A10); also elsewhere on the board
D2: U$1.11 (D2), U$3.PB10 (B10); also elsewhere on the board
D3: U$1.9 (D3), U$3.PA11 (A11); also elsewhere on the board
D4: U$1.7 (D4), U$3.PB11 (B11); also elsewhere on the board
D5: U$1.5 (D5), U$3.PA12 (A12); also elsewhere on the board
D6: U$1.3 (D6), U$3.PB12 (B12); also elsewhere on the board
D7: U$1.1 (D7), U$3.PA13 (A13); also elsewhere on the board
GND: U$1.18 (GND), U$1.35 (GND), U$3.SHIELD1 (SHIELD), U$3.SHIELD2 (SHIELD), U$3.SHIELD3 (SHIELD), U$3.SHIELD4 (SHIELD), U$3.SHIELD5 (SHIELD), U$3.SHIELD6 (SHIELD); also elsewhere on the board
R/!W!: U$1.27 (R/!W!), U$3.PB17 (B17)
RD4: U$1.43 (RD4), U$3.PB15 (B15)
RD5: U$1.45 (RD5), U$3.PA16 (A16)

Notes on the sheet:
High voltage signals
Parts Verified

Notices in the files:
boards/xio2/xio2.brd:
© 2018 SjG
boards/xio3/xio3.brd:
© 2019 SjG
parts and their libraries:
microbuilder: This work is placed in the public domain, and may be freely used for commercial and non-commercial work with the following conditions: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
SparkFun: Licensing: CC v3.0 Share-Alike You are welcome to use this library for commercial purposes.
